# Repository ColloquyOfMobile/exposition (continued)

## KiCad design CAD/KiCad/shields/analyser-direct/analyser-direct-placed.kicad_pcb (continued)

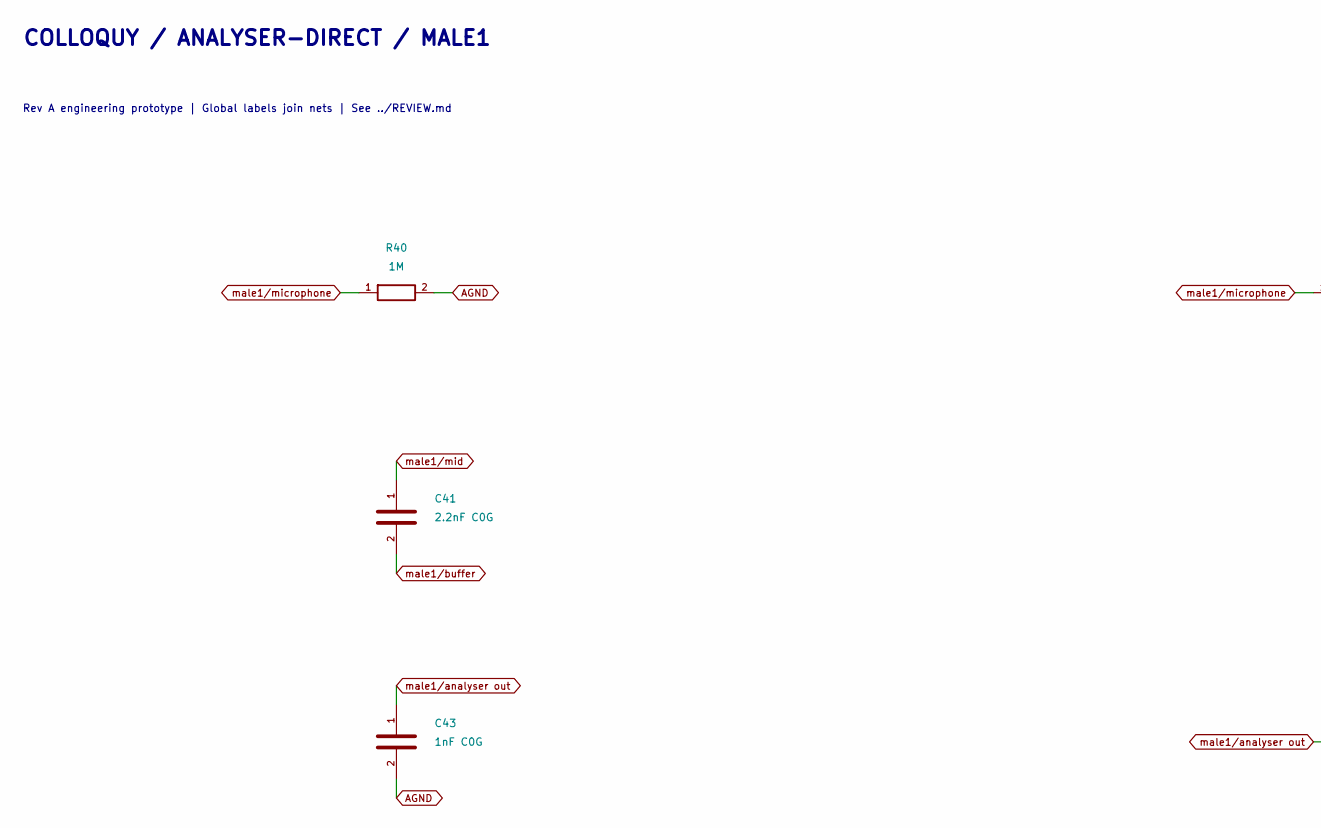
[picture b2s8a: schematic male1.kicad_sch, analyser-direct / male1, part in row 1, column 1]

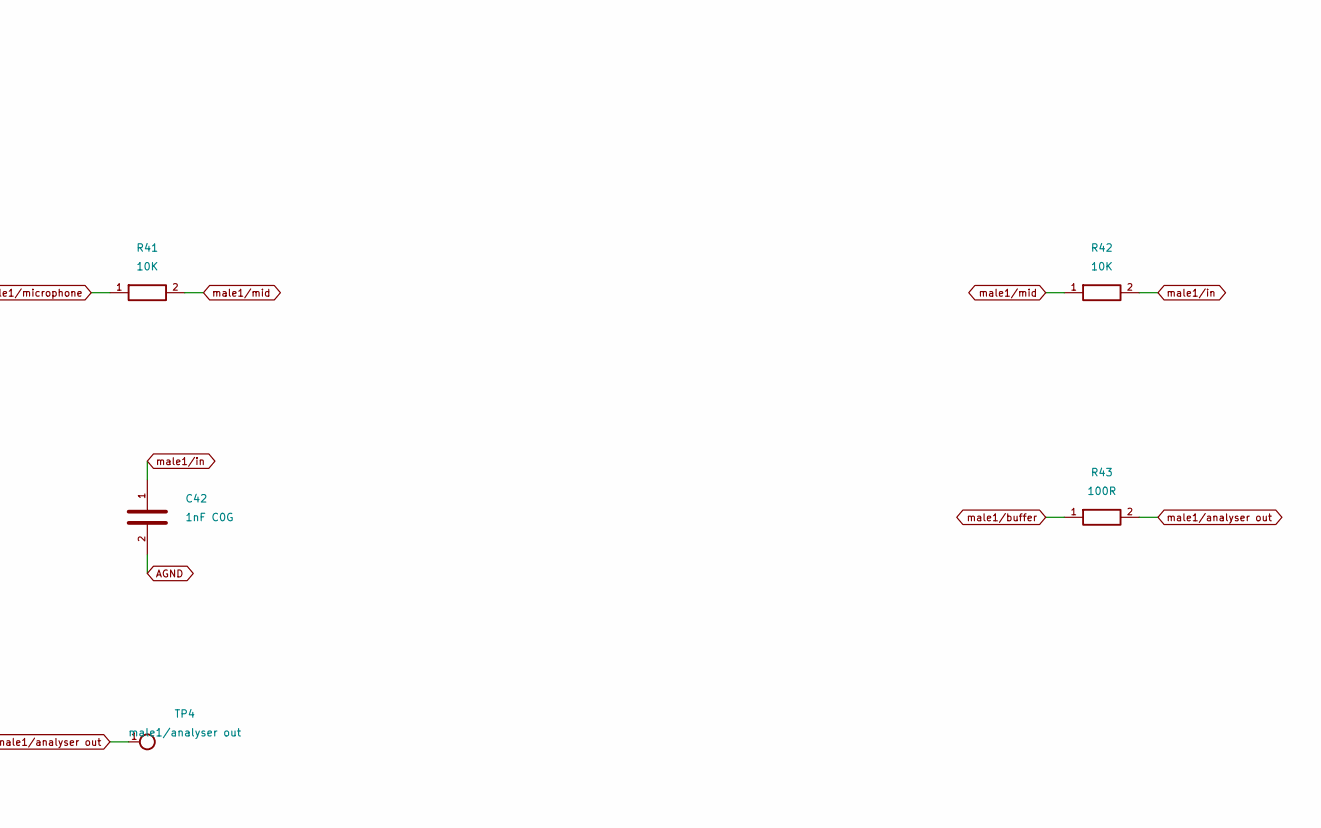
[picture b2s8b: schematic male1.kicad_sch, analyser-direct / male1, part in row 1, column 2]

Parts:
C41: 2.2nF C0G; C_0603_1608Metric
C42, C43: 1nF C0G; C_0603_1608Metric
R40: 1M; R_0603_1608Metric
R41, R42: 10K; R_0603_1608Metric
R43: 100R; R_0603_1608Metric
TP4: male1/analyser out; TestPoint_Pad_D1.5mm

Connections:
AGND: C42.2, C43.2, R40.2; also elsewhere on the board
male1/analyser out: C43.1, R43.2, TP4.1; also elsewhere on the board
male1/buffer: C41.2, R43.1; also elsewhere on the board
male1/in: C42.1, R42.2; also elsewhere on the board
male1/microphone: R40.1, R41.1; also elsewhere on the board
male1/mid: C41.1, R41.2, R42.1

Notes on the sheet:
COLLOQUY / ANALYSER-DIRECT / MALE1
Rev A engineering prototype | Global labels join nets | See ../REVIEW.md

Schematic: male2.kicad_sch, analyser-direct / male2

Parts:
C51: 2.2nF C0G; C_0603_1608Metric
C52, C53: 1nF C0G; C_0603_1608Metric
R50: 1M; R_0603_1608Metric
R51, R52: 10K; R_0603_1608Metric
R53: 100R; R_0603_1608Metric
TP5: male2/analyser out; TestPoint_Pad_D1.5mm

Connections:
AGND: C52.2, C53.2, R50.2; also elsewhere on the board
male2/analyser out: C53.1, R53.2, TP5.1; also elsewhere on the board
male2/buffer: C51.2, R53.1; also elsewhere on the board
male2/in: C52.1, R52.2; also elsewhere on the board
male2/microphone: R50.1, R51.1; also elsewhere on the board
male2/mid: C51.1, R51.2, R52.1

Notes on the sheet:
COLLOQUY / ANALYSER-DIRECT / MALE2
Rev A engineering prototype | Global labels join nets | See ../REVIEW.md

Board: 2 copper layers, 53 parts (1 on the bottom side), 33 nets, no tracks yet.

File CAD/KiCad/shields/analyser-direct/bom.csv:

Reference,Value,Footprint,MPN,Assembly
JA1,ANALYSER - KEY 22,Shields:Socket_2x11_Key22,,fit
JB1,BENCH GND +5V SIGNAL,Shields:JST_EH_B3B-EH-A_1x03_P2.50mm_Vertical,,fit
R10,1M,Shields:R_0603_1608Metric,,fit
R11,10K,Shields:R_0603_1608Metric,,fit
R12,10K,Shields:R_0603_1608Metric,,fit
C11,2.2nF C0G,Shields:C_0603_1608Metric,,fit
C12,1nF C0G,Shields:C_0603_1608Metric,,fit
R13,100R,Shields:R_0603_1608Metric,,fit
C13,1nF C0G,Shields:C_0603_1608Metric,,fit
R20,1M,Shields:R_0603_1608Metric,,fit
R21,10K,Shields:R_0603_1608Metric,,fit
R22,10K,Shields:R_0603_1608Metric,,fit
C21,2.2nF C0G,Shields:C_0603_1608Metric,,fit
C22,1nF C0G,Shields:C_0603_1608Metric,,fit
R23,100R,Shields:R_0603_1608Metric,,fit
C23,1nF C0G,Shields:C_0603_1608Metric,,fit
R30,1M,Shields:R_0603_1608Metric,,fit
R31,10K,Shields:R_0603_1608Metric,,fit
R32,10K,Shields:R_0603_1608Metric,,fit
C31,2.2nF C0G,Shields:C_0603_1608Metric,,fit
C32,1nF C0G,Shields:C_0603_1608Metric,,fit
R33,100R,Shields:R_0603_1608Metric,,fit
C33,1nF C0G,Shields:C_0603_1608Metric,,fit
R40,1M,Shields:R_0603_1608Metric,,fit
R41,10K,Shields:R_0603_1608Metric,,fit
R42,10K,Shields:R_0603_1608Metric,,fit
C41,2.2nF C0G,Shields:C_0603_1608Metric,,fit
C42,1nF C0G,Shields:C_0603_1608Metric,,fit
R43,100R,Shields:R_0603_1608Metric,,fit
C43,1nF C0G,Shields:C_0603_1608Metric,,fit
R50,1M,Shields:R_0603_1608Metric,,fit
R51,10K,Shields:R_0603_1608Metric,,fit
R52,10K,Shields:R_0603_1608Metric,,fit
C51,2.2nF C0G,Shields:C_0603_1608Metric,,fit
C52,1nF C0G,Shields:C_0603_1608Metric,,fit
R53,100R,Shields:R_0603_1608Metric,,fit
C53,1nF C0G,Shields:C_0603_1608Metric,,fit
U1,MCP6004-I/SL,Shields:SOIC-14_3.9x8.7mm_P1.27mm,MCP6004-I/SL,fit
CB1,100nF,Shields:C_0603_1608Metric,,fit
CBU1,10uF X7R,Shields:C_0805_2012Metric,,fit
U2,MCP6004-I/SL,Shields:SOIC-14_3.9x8.7mm_P1.27mm,MCP6004-I/SL,fit
CB2,100nF,Shields:C_0603_1608Metric,,fit
CBU2,10uF X7R,Shields:C_0805_2012Metric,,fit

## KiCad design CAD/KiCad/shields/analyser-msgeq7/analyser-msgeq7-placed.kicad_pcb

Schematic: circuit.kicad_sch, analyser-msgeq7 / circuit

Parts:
TPG: AGND; TestPoint_Pad_D1.5mm
TPI: IOREF; TestPoint_Pad_D1.5mm
TPR: analyser/reset; TestPoint_Pad_D1.5mm
TPS: analyser/strobe; TestPoint_Pad_D1.5mm

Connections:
AGND: TPG.1; also elsewhere on the board
IOREF: TPI.1; also elsewhere on the board
analyser/reset: TPR.1; also elsewhere on the board
analyser/strobe: TPS.1; also elsewhere on the board

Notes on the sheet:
COLLOQUY / ANALYSER-MSGEQ7 / CIRCUIT
Rev A engineering prototype | Global labels join nets | See ../REVIEW.md

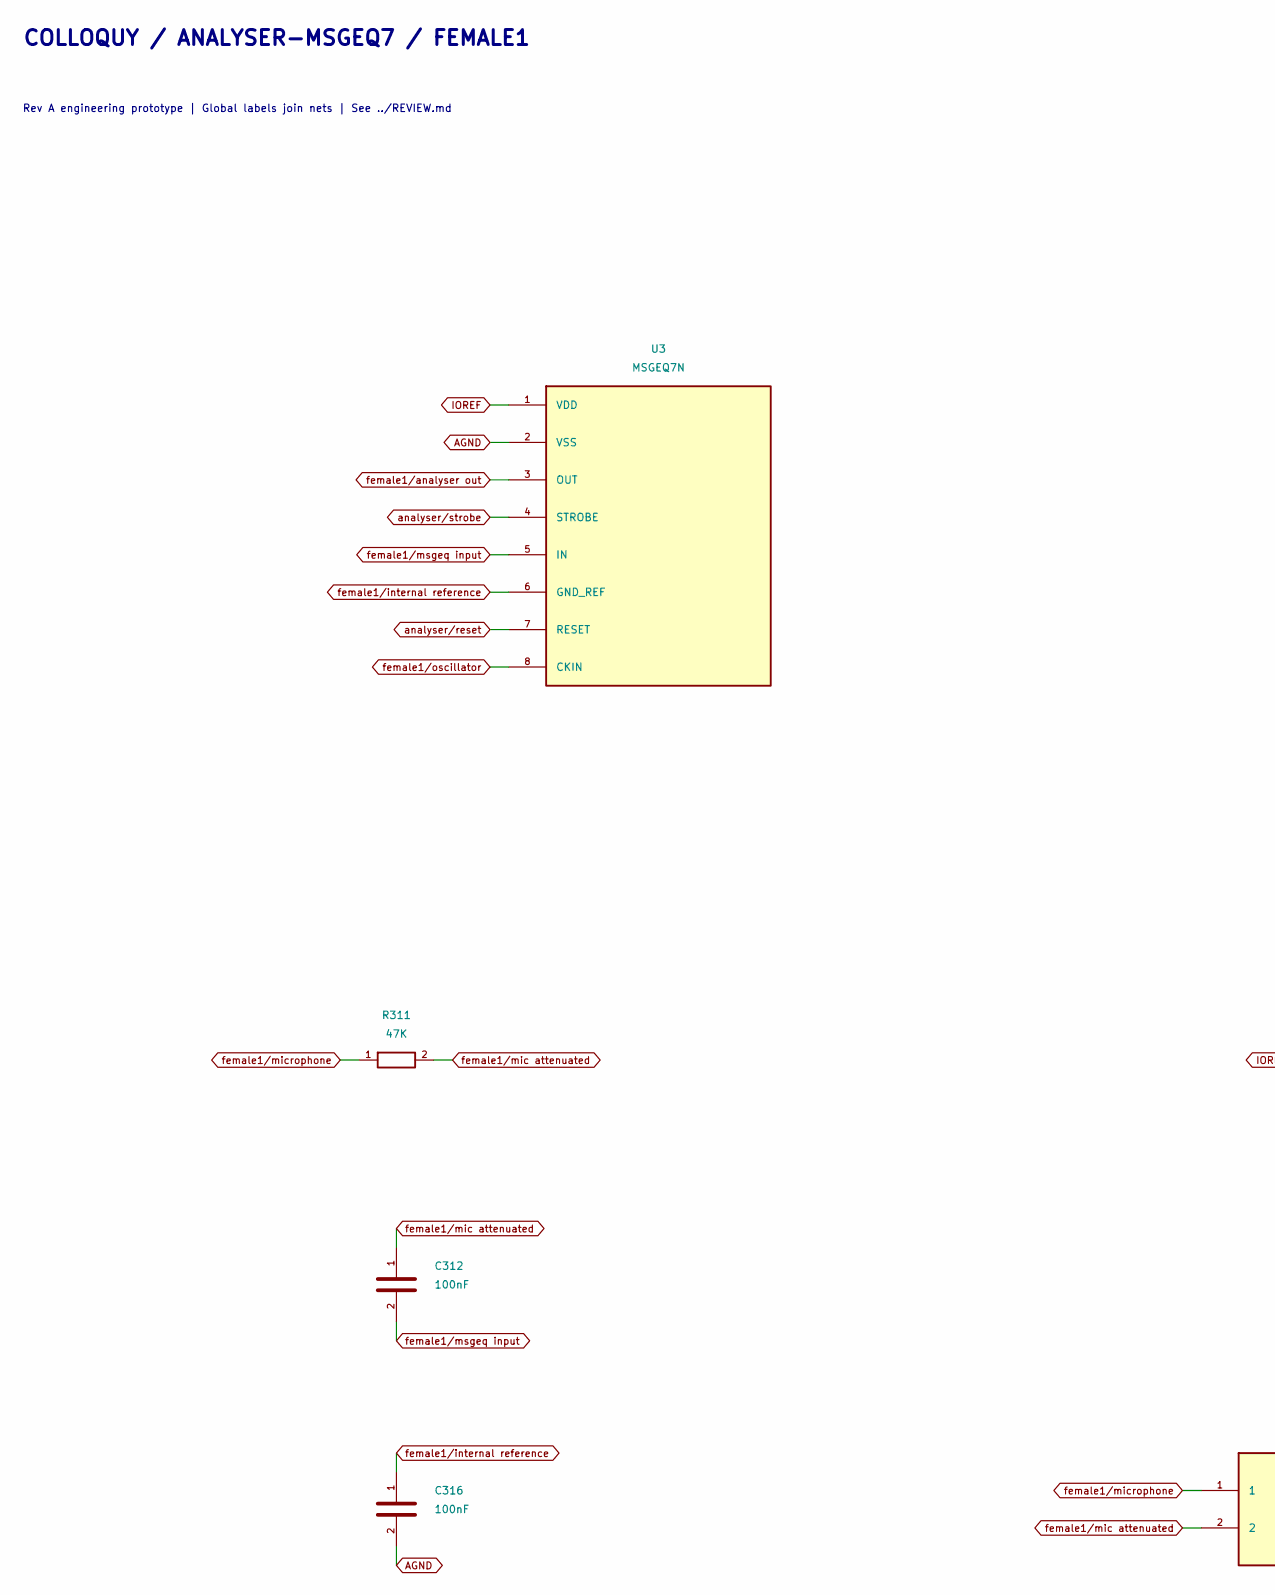
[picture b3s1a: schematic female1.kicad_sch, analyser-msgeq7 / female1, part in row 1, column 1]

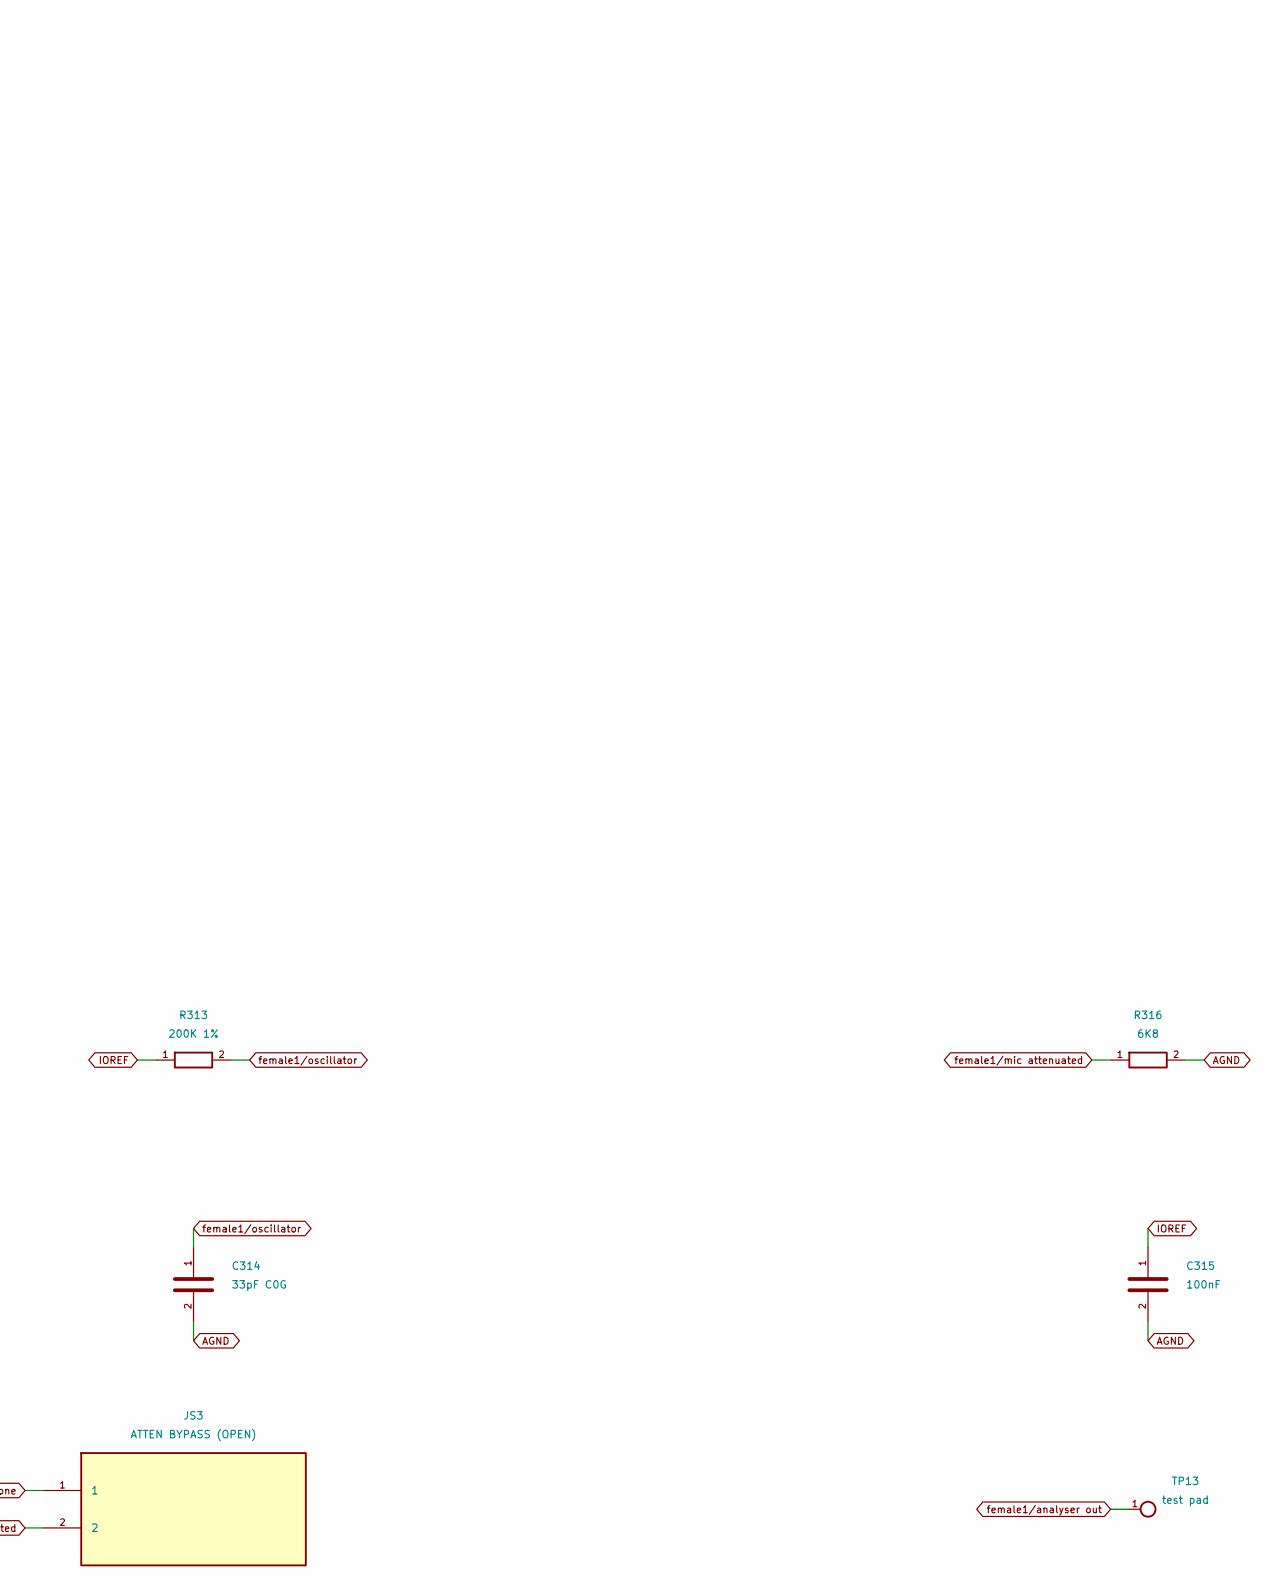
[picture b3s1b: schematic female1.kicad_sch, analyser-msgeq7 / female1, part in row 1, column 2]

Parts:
C312, C315, C316: 100nF; C_0603_1608Metric
C314: 33pF C0G; C_0603_1608Metric
JS3: ATTEN BYPASS (OPEN); SolderJumper-2_P1.3mm_Open_RoundedPad1.0x1.5mm
R311: 47K; R_0603_1608Metric
R313: 200K 1%; R_0603_1608Metric
R316: 6K8; R_0603_1608Metric
TP13: test pad; TestPoint_Pad_D1.5mm
U3: MSGEQ7N; SOIC-8_3.9x4.9mm_P1.27mm

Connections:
AGND: C314.2, C315.2, C316.2, R316.2, U3.2 (VSS); also elsewhere on the board
IOREF: C315.1, R313.1, U3.1 (VDD); also elsewhere on the board
analyser/reset: U3.7 (RESET); also elsewhere on the board
analyser/strobe: U3.4 (STROBE); also elsewhere on the board
female1/analyser out: TP13.1, U3.3 (OUT); also elsewhere on the board
female1/internal reference: C316.1, U3.6 (GND_REF)
female1/mic attenuated: C312.1, JS3.2, R311.2, R316.1
female1/microphone: JS3.1, R311.1; also elsewhere on the board
female1/msgeq input: C312.2, U3.5 (IN)
female1/oscillator: C314.1, R313.2, U3.8 (CKIN)

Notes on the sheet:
COLLOQUY / ANALYSER-MSGEQ7 / FEMALE1
Rev A engineering prototype | Global labels join nets | See ../REVIEW.md

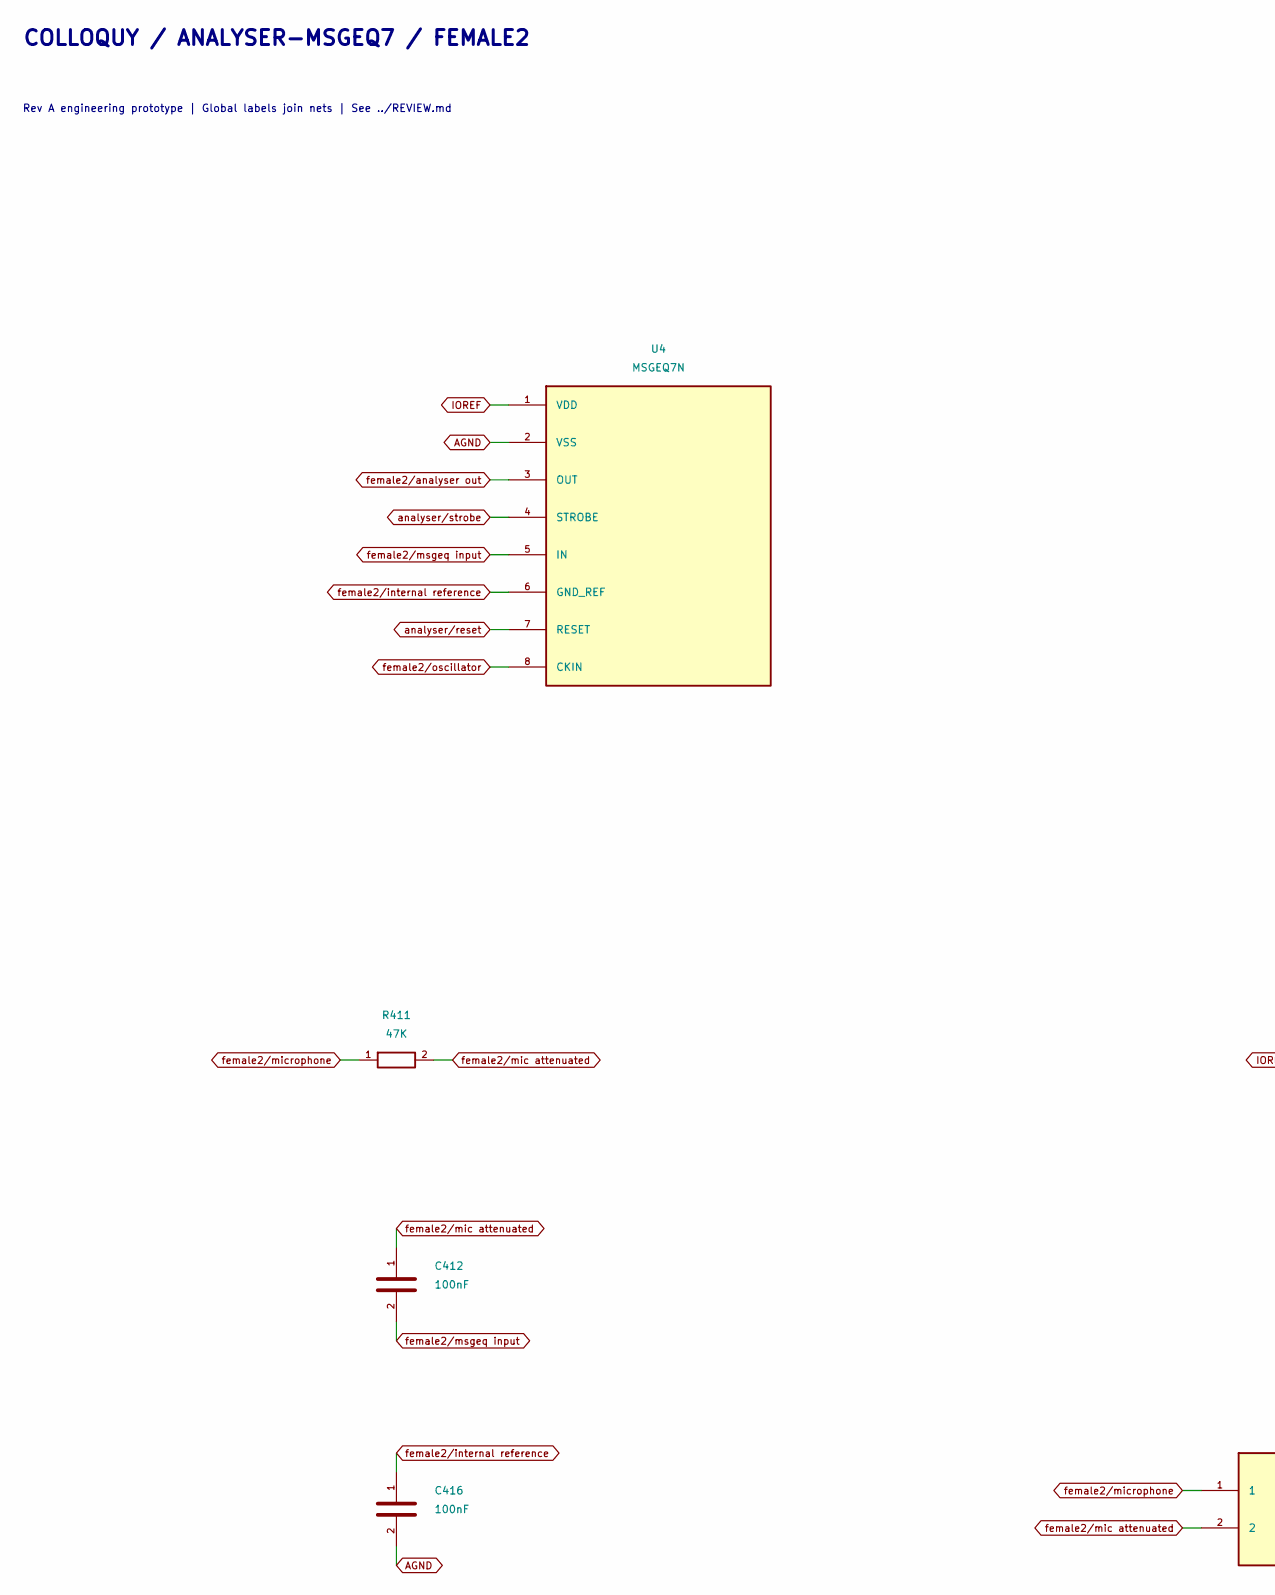
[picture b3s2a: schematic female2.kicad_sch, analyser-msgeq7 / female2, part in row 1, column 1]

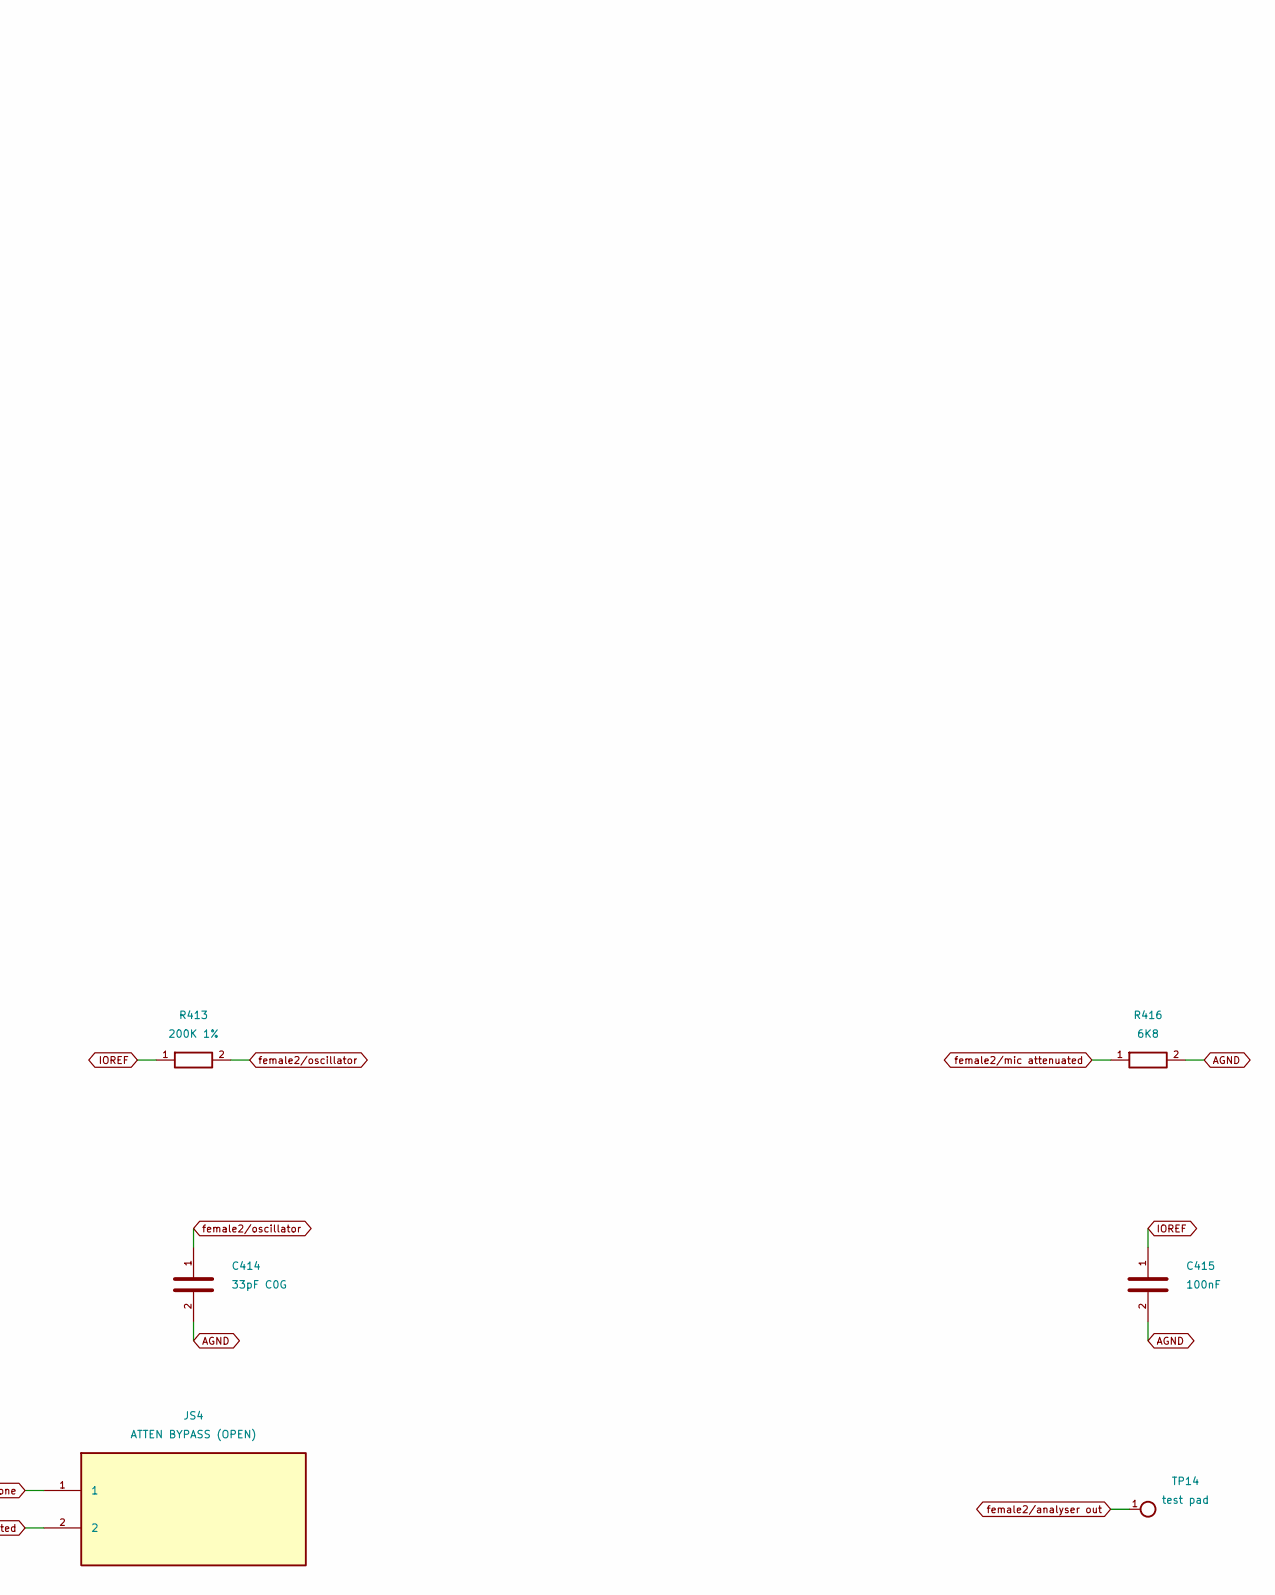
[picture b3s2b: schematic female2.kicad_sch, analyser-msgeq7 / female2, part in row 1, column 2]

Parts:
C412, C415, C416: 100nF; C_0603_1608Metric
C414: 33pF C0G; C_0603_1608Metric
JS4: ATTEN BYPASS (OPEN); SolderJumper-2_P1.3mm_Open_RoundedPad1.0x1.5mm
R411: 47K; R_0603_1608Metric
R413: 200K 1%; R_0603_1608Metric
R416: 6K8; R_0603_1608Metric
TP14: test pad; TestPoint_Pad_D1.5mm
U4: MSGEQ7N; SOIC-8_3.9x4.9mm_P1.27mm

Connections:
AGND: C414.2, C415.2, C416.2, R416.2, U4.2 (VSS); also elsewhere on the board
IOREF: C415.1, R413.1, U4.1 (VDD); also elsewhere on the board
analyser/reset: U4.7 (RESET); also elsewhere on the board
analyser/strobe: U4.4 (STROBE); also elsewhere on the board
female2/analyser out: TP14.1, U4.3 (OUT); also elsewhere on the board
female2/internal reference: C416.1, U4.6 (GND_REF)
female2/mic attenuated: C412.1, JS4.2, R411.2, R416.1
female2/microphone: JS4.1, R411.1; also elsewhere on the board
female2/msgeq input: C412.2, U4.5 (IN)
female2/oscillator: C414.1, R413.2, U4.8 (CKIN)

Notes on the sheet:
COLLOQUY / ANALYSER-MSGEQ7 / FEMALE2
Rev A engineering prototype | Global labels join nets | See ../REVIEW.md

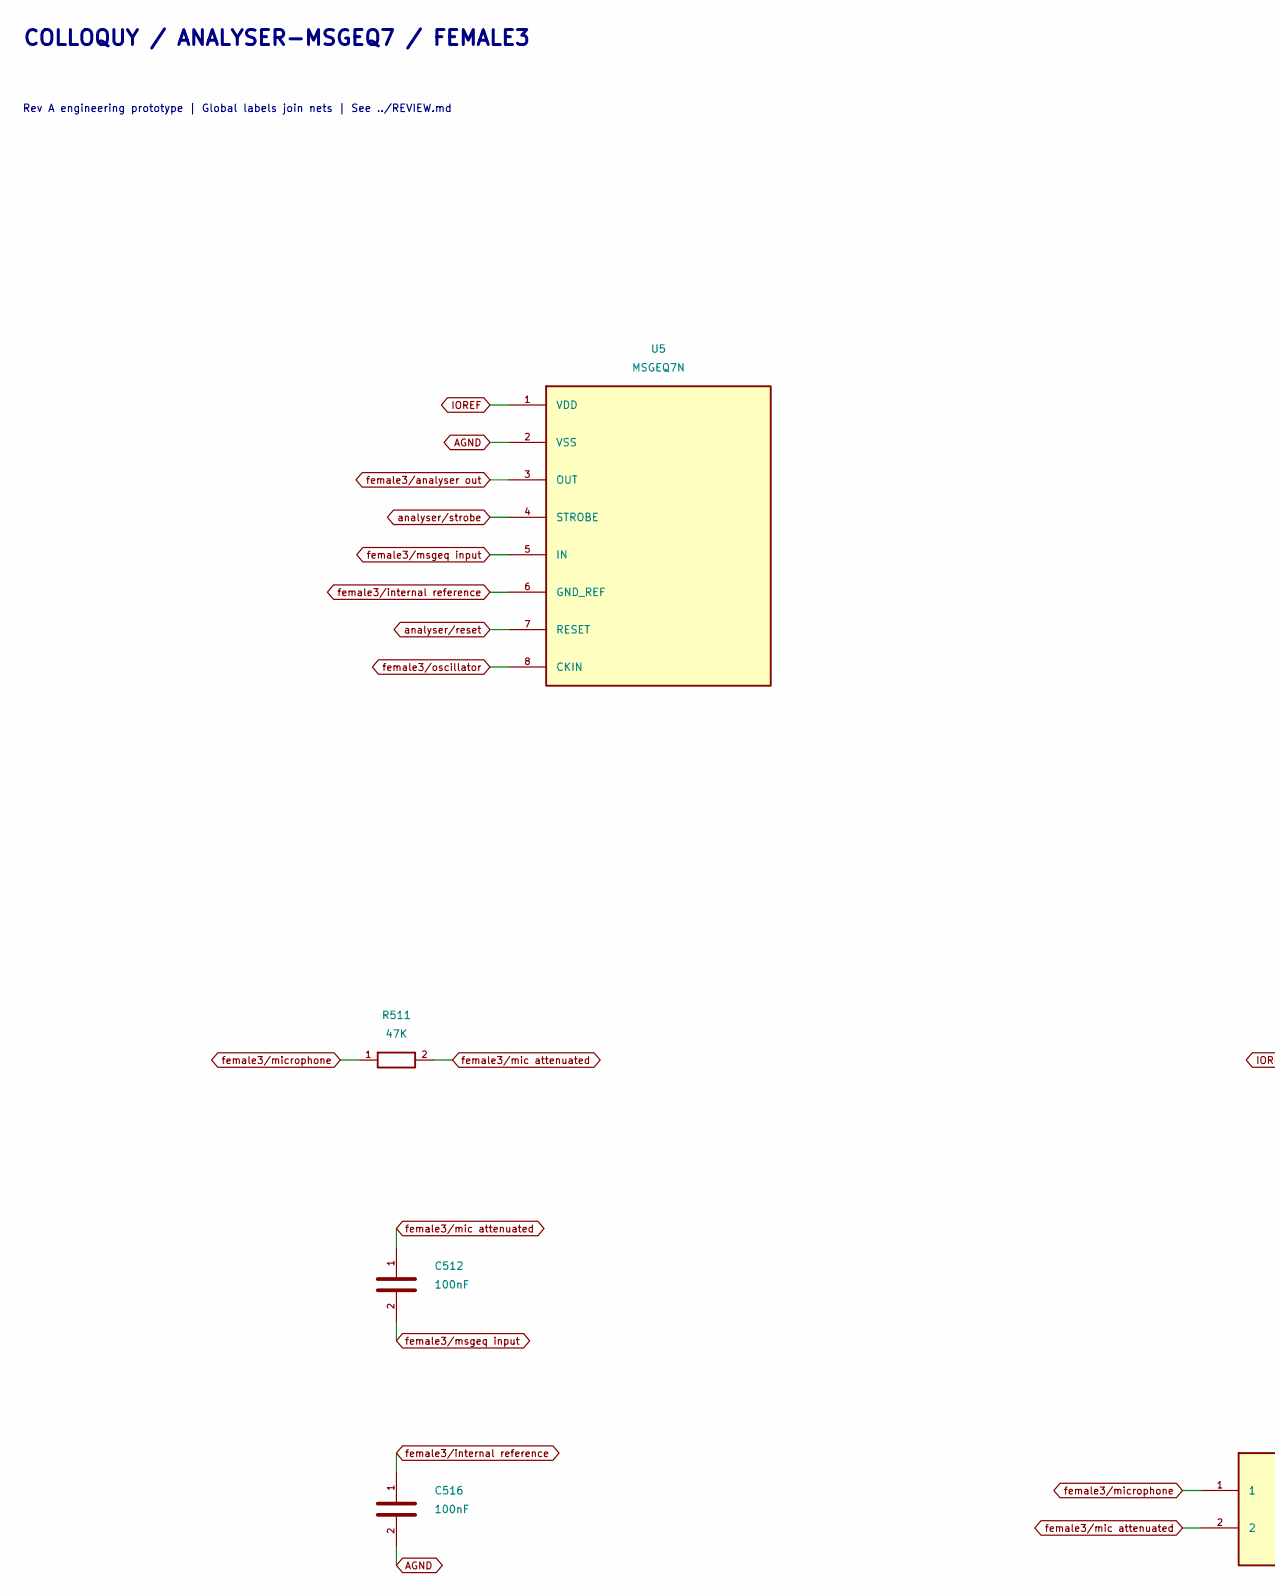
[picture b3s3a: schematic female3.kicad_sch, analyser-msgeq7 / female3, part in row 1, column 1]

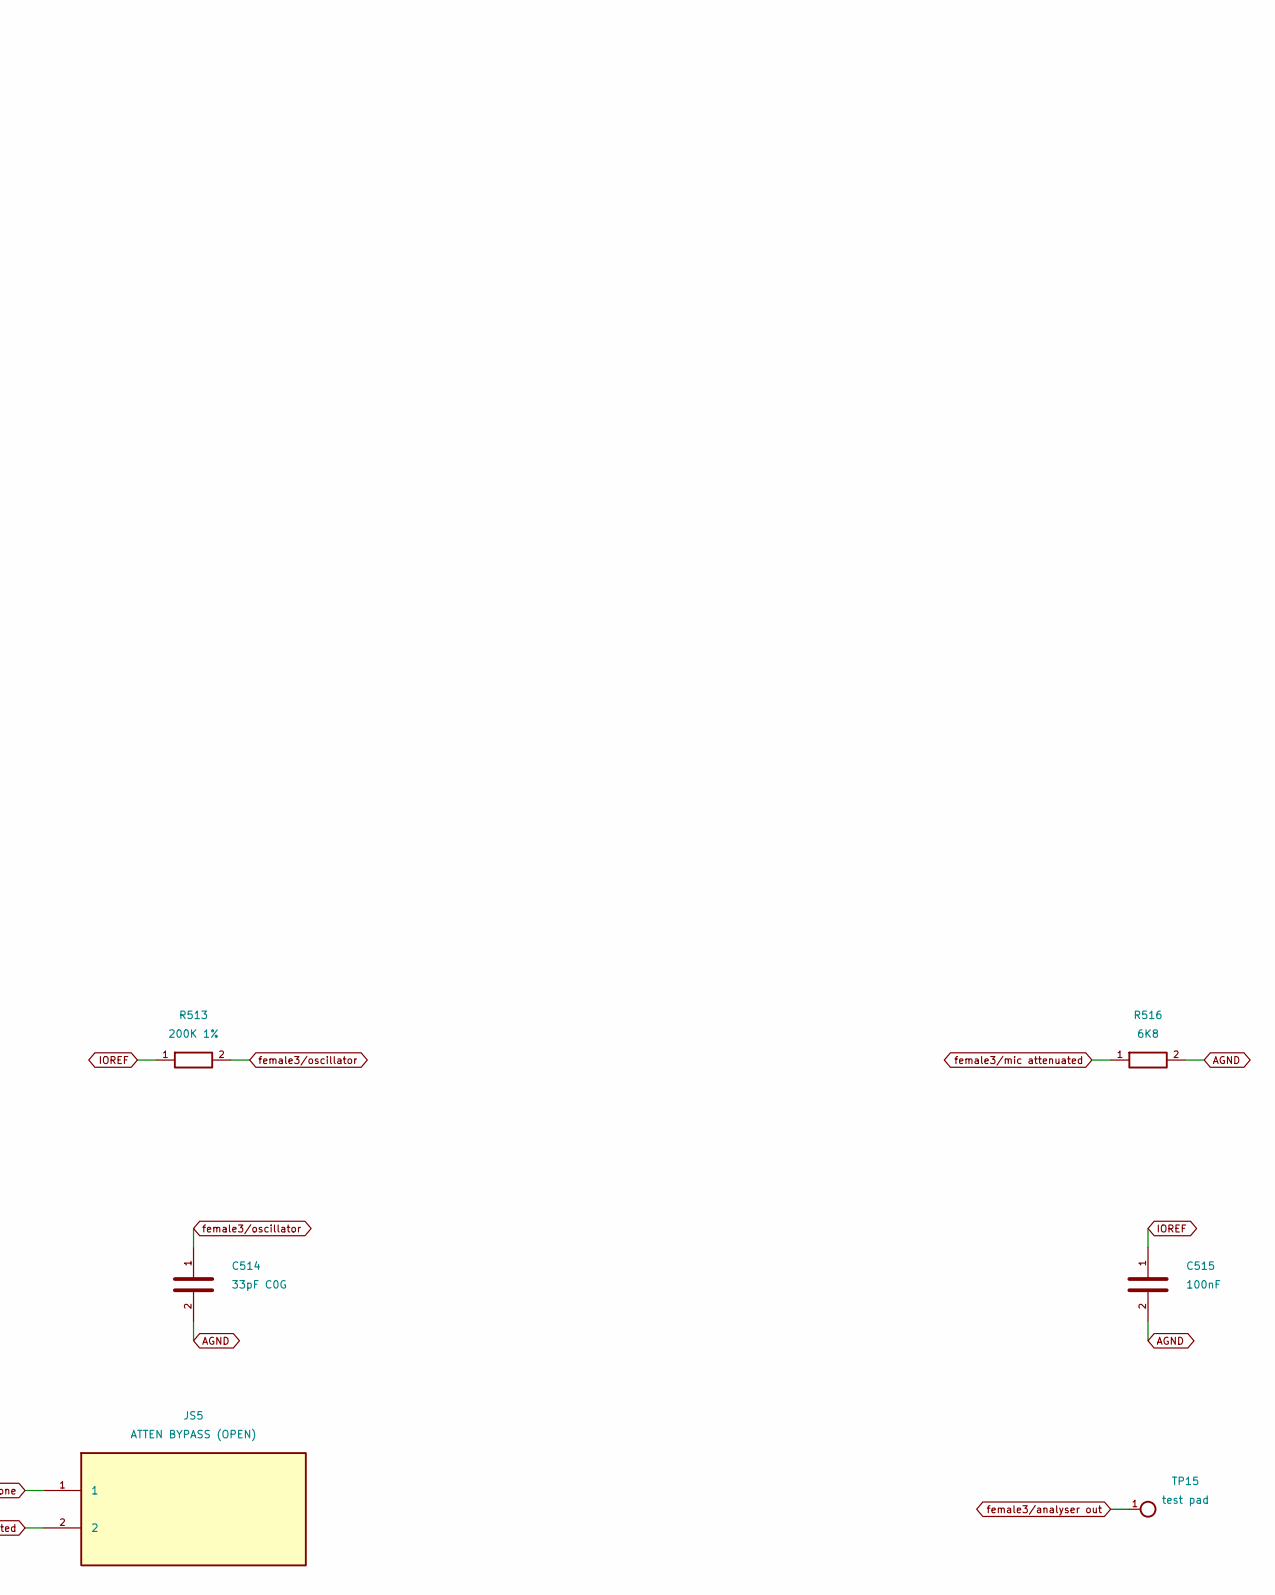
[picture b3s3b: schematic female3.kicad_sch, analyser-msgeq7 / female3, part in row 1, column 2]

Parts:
C512, C515, C516: 100nF; C_0603_1608Metric
C514: 33pF C0G; C_0603_1608Metric
JS5: ATTEN BYPASS (OPEN); SolderJumper-2_P1.3mm_Open_RoundedPad1.0x1.5mm
R511: 47K; R_0603_1608Metric
R513: 200K 1%; R_0603_1608Metric
R516: 6K8; R_0603_1608Metric
TP15: test pad; TestPoint_Pad_D1.5mm
U5: MSGEQ7N; SOIC-8_3.9x4.9mm_P1.27mm

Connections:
AGND: C514.2, C515.2, C516.2, R516.2, U5.2 (VSS); also elsewhere on the board
IOREF: C515.1, R513.1, U5.1 (VDD); also elsewhere on the board
analyser/reset: U5.7 (RESET); also elsewhere on the board
analyser/strobe: U5.4 (STROBE); also elsewhere on the board
female3/analyser out: TP15.1, U5.3 (OUT); also elsewhere on the board
female3/internal reference: C516.1, U5.6 (GND_REF)
female3/mic attenuated: C512.1, JS5.2, R511.2, R516.1
female3/microphone: JS5.1, R511.1; also elsewhere on the board
female3/msgeq input: C512.2, U5.5 (IN)
female3/oscillator: C514.1, R513.2, U5.8 (CKIN)

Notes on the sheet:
COLLOQUY / ANALYSER-MSGEQ7 / FEMALE3
Rev A engineering prototype | Global labels join nets | See ../REVIEW.md

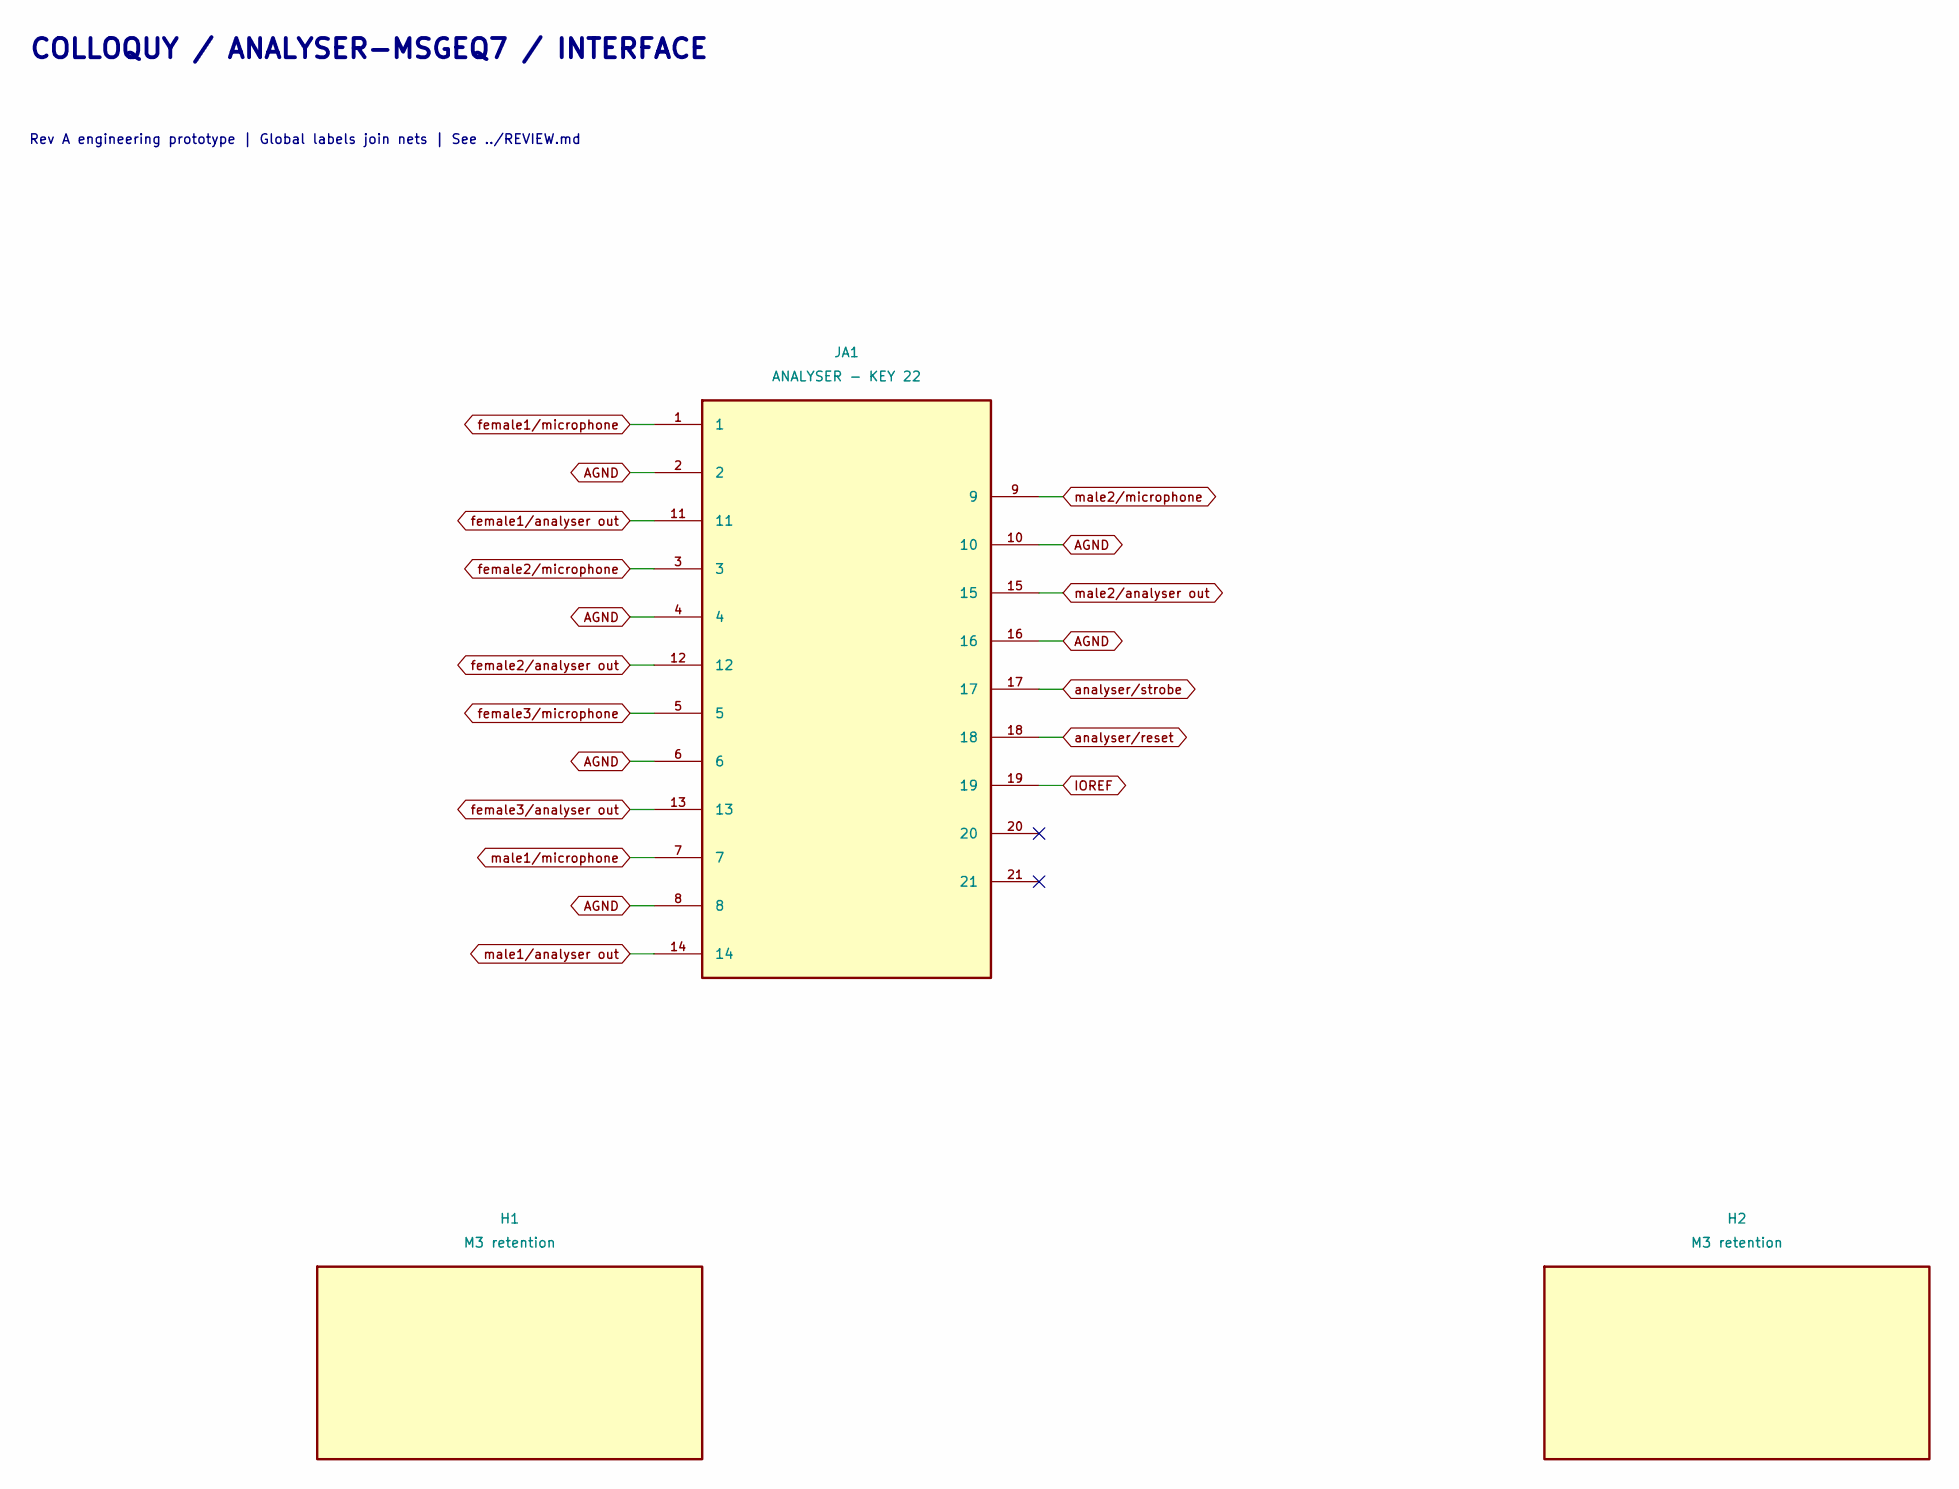
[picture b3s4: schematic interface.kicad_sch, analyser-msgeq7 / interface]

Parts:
H1, H2: M3 retention; MountingHole_3.2mm_M3
JA1: ANALYSER - KEY 22; Socket_2x11_Key22

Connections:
AGND: JA1.2, JA1.4, JA1.6, JA1.8, JA1.10, JA1.16; also elsewhere on the board
IOREF: JA1.19; also elsewhere on the board
analyser/reset: JA1.18; also elsewhere on the board
analyser/strobe: JA1.17; also elsewhere on the board
female1/analyser out: JA1.11; also elsewhere on the board
female1/microphone: JA1.1; also elsewhere on the board
female2/analyser out: JA1.12; also elsewhere on the board
female2/microphone: JA1.3; also elsewhere on the board
female3/analyser out: JA1.13; also elsewhere on the board
female3/microphone: JA1.5; also elsewhere on the board
male1/analyser out: JA1.14; also elsewhere on the board
male1/microphone: JA1.7; also elsewhere on the board
male2/analyser out: JA1.15; also elsewhere on the board
male2/microphone: JA1.9; also elsewhere on the board

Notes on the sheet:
COLLOQUY / ANALYSER-MSGEQ7 / INTERFACE
Rev A engineering prototype | Global labels join nets | See ../REVIEW.md
